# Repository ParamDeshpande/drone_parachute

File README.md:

# taxir 
This is the repository for the problem statement 
```
Develop a mechanism (can be software/ hardware/ both ) to deploy a parachute installed on the UAV in case of an emergency landing or power outage. The parachute is placed inside a compartment.
The expected output "Can be in the form of validated electronic circuit design, parachute deployment mechanism, CAD design, code, hardware"
(The code can be written in any programming language of your choice)
```
## Code
There are few versions of the code, please find the latest one in arduino_version. STM_32 mbed version is deprecated has memory overflow issues. 
find the cpp files in /main headers in /include.
 
## Setup

### Mainframe SETUP 

Please do install PlatformIO extension in VSCODE or the arduino IDE, in your pc/laptop depending on which architecture and which is being used or any other if you know what you are doing .... . and do install any HC-05 bluetooth serial terminal. Like [this one](https://play.google.com/store/apps/details?id=de.kai_morich.serial_bluetooth_terminal&hl=en). Or any other as per your preference.

### The system SETUP

Connect the backup battery and main battery in any order whatsover, the system should give an error and should fire the parachute initially cause one of the battery was missing. (new feature or setup init needs to be added here). That way even the end user is assured of the system working.
**HIT THE RESET BUTTON**
Connect your device to get debug via bluetooth, as to what is happening, if everything works out good, you will get debug message on bt stating all's good, else you might find the buzzer still irritating you. And there you go The system is up and ready.

## Conditions 
To eject the parachute, we apply the condition that it must reach a certain speed (1.5 m/s) or more within a specified time interval (0.25 s)
ie an acceleration of about 6m/secsq
. Otherwise, the parachute will not be ejected. Under such conditions, the drone is not allowed to reach a dangerous fall speed.

## Effects ( aka what all is done )
Once the parachute deploys, the system stops the spinning rotors to avoid entanglement with the parachute cords and reduces the risk of laceration injuries to people on the ground.
If battery dies out
relays releases spring support for the chute lid , 
Manual 
Release the flow for the chute aka stop powering the relay to hold the lid
Automatic 
FAILSAFE MECHANISM : The above mentioned in code. 

EITHER WAY OPENS under the given or desired conditions.

## PROTOTYPE GPB VERSION.

SEE  drone_parachute_pcb folder for board schematic.

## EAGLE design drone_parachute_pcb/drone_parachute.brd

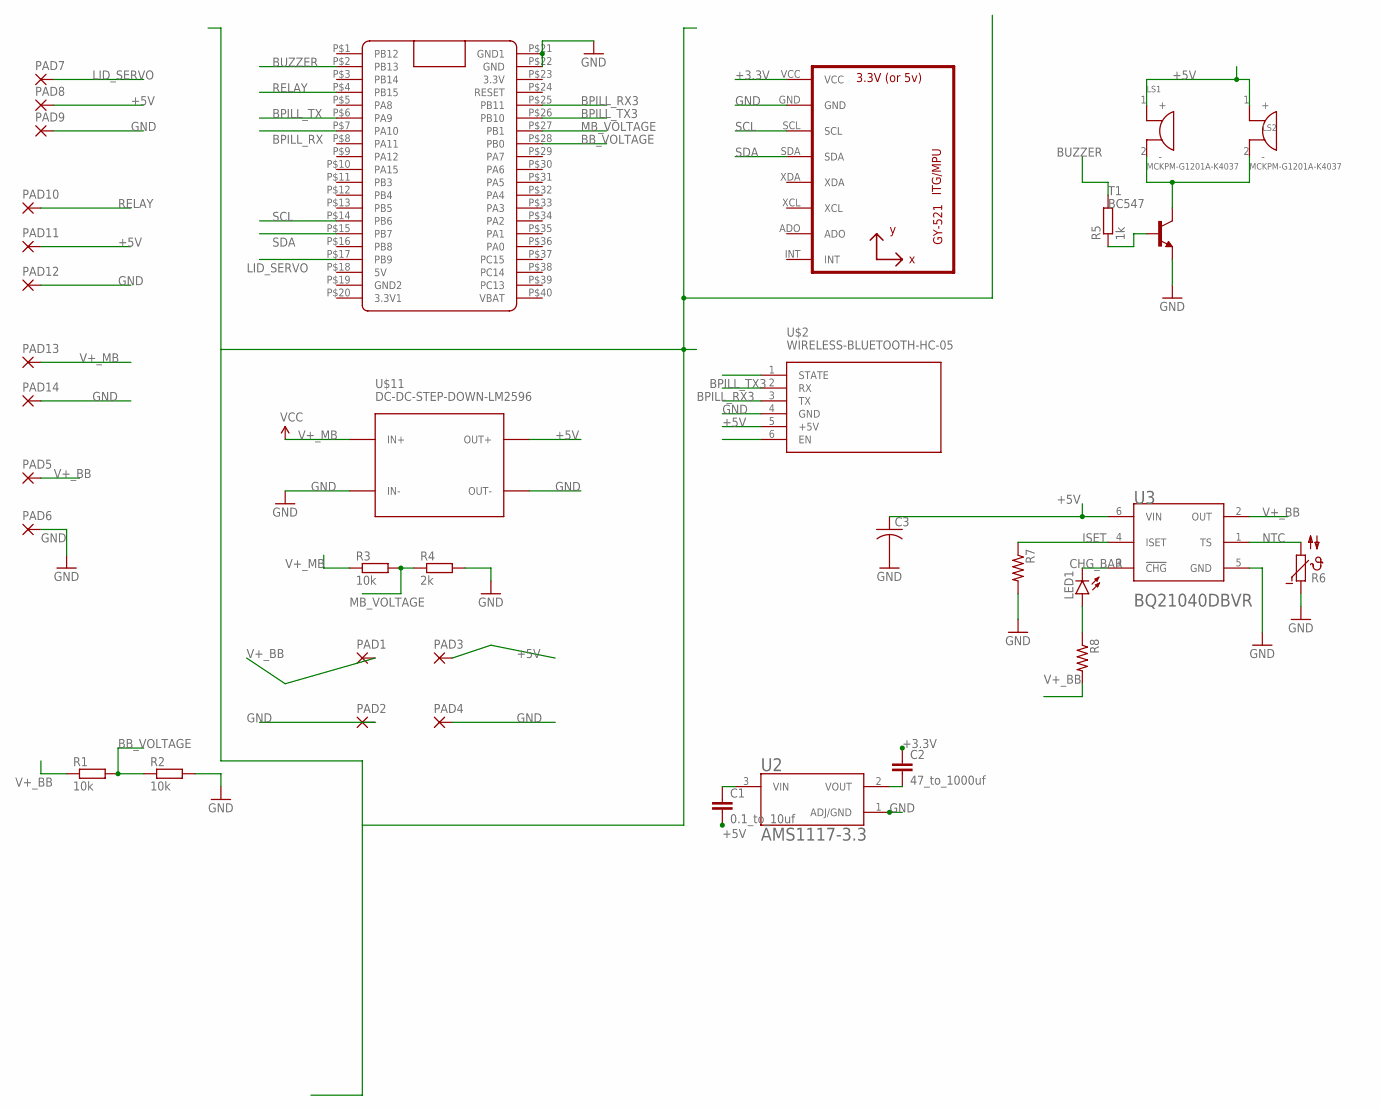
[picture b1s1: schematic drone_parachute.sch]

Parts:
C1: 0.1_to_10uf; C025-025X050
C2: 47_to_1000uf; C025-025X050
C3: C-USC0805; C0805
LED1: LEDCHIP-LED0805; CHIP-LED0805
LS1, LS2: MCKPM-G1201A-K4037; XDCR_MCKPM-G1201A-K4037
PAD1, PAD2, PAD3, PAD4, PAD5, PAD6, PAD7, PAD8, PAD9, PAD10, PAD11, PAD12, PAD13, PAD14: 1,6/0,8
R1, R2, R3: 10k; 0204/7
R4: 2k; 0204/7
R5: 1k; 0204/7
R6: NTC640; P640
R7, R8: R-US_R0805; R0805
T1: BC547; TO92
U1: GY-521MPU6050; GY-521
U2: AMS1117-3.3; SOT229P700X180-4N
U3: TEXAS_INSTRUMENTS_BQ21040DBVRTEXAS_INSTRUMENTS_BQ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; TEXAS_INSTRUMENTS_BQ21040DBVR_0
U$1: BLUE_PILL
U$2: WIRELESS-BLUETOOTH-HC-05
U$11: DC-DC-STEP-DOWN-LM2596

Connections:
+3.3V: C2.1, U1.VCC
+5V: C1.2, C3.1, LS1.1 (+), LS2.1 (+), PAD3.1, PAD8.1, PAD11.1, U3.6 (VIN), U$2.5 (+5V), U$11.OUT+
BB_VOLTAGE: R1.2, R2.1, U$1.P$28 (PB0)
BPILL_RX: U$1.P$7 (PA10)
BPILL_RX3: U$1.P$25 (PB11), U$2.3 (TX)
BPILL_TX: U$1.P$6 (PA9)
BPILL_TX3: U$1.P$26 (PB10), U$2.2 (RX)
BUZZER: R5.2, U$1.P$2 (PB13)
CHG_BAR: LED1.C, U3.3 (!CHG!)
GND: C3.2, PAD2.1, PAD4.1, PAD6.1, PAD9.1, PAD12.1, PAD14.1, R2.2, R4.2, R6.1, R7.2, T1.1 (E), U1.GND, U2.1 (ADJ/GND), U3.5 (GND), U$1.P$21 (GND1), U$1.P$22 (GND), U$2.4 (GND), U$11.IN-, U$11.OUT-
ISET: R7.1, U3.4 (ISET)
LID_SERVO: PAD7.1, U$1.P$17 (PB9)
MB_VOLTAGE: R3.2, R4.1, U$1.P$27 (PB1)
unnamed: C1.1, U2.3 (VIN)
unnamed: R5.1, T1.2 (B)
unnamed: C2.2, U2.2 (VOUT)
unnamed: LED1.A, R8.1
unnamed: LS1.2 (-), LS2.2 (-), T1.3 (C)
NTC: R6.2, U3.1 (TS)
RELAY: PAD10.1, U$1.P$4 (PB15)
SCL: U1.SCL, U$1.P$14 (PB6)
SDA: U1.SDA, U$1.P$15 (PB7)
V+_BB: PAD1.1, PAD5.1, R1.1, R8.2, U3.2 (OUT)
V+_MB: PAD13.1, R3.1, U$11.IN+

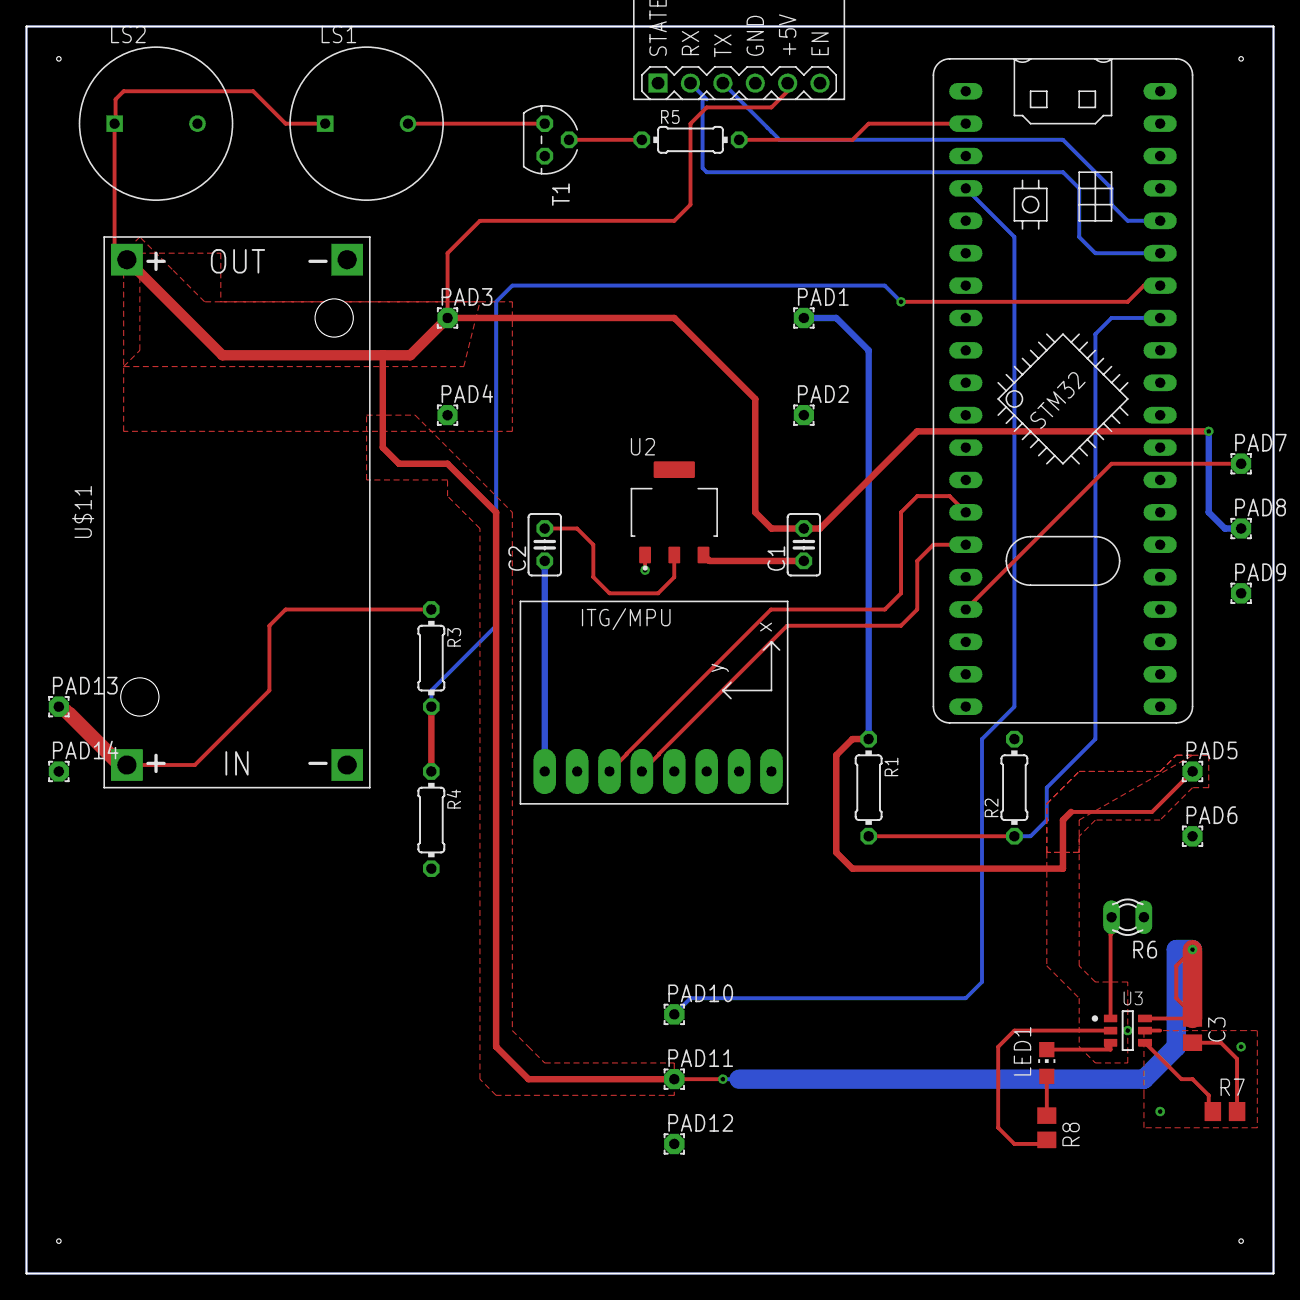
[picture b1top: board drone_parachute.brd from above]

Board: 2 copper layers, 97.8 x 97.8 mm, 35 parts (0 on the bottom side), 22 nets.

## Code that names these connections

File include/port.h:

#ifndef PORT_H
#define PORT_H

//enum PIN_Nos{PA2,PA3,PB0,PB1,PB6,PB7,PB9,PB13,PB15,PC13};


const int RX = (PA3) ;
const int TX = (PA2) ;
const int SCL = (PB6) ;
const int SDA = (PB7) ;
const int LED_PIN = (PC13);
const int SERVO_PIN = (PB9);
const int RELAY_PIN = (PB15);
const int BUZZER_PIN = (PB13);
const int MAIN_BAT_VOLT_PIN = (PB1);
const int BACKUP_BAT_VOLT_PIN = (PB0);

#endif // !PORT_H

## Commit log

2020-01-04 added things from taxir task2
2020-01-04 blink led code works
2020-01-05 added lot of things
2020-01-08 added code for arduino version
2020-01-08 arduino works only when files are named as .ino
2020-01-08 firsst commit
2020-01-08 big picture commit
2020-01-09 partially written battery.ino
2020-01-09 changed src to main and added include folder in main
2020-01-09 big picutre commit
2020-01-09 big picture commit #3
2020-01-09 big commit
2020-01-16 added PCB design.
2020-01-16 added GPB images.
2020-01-16 added img in readme
2020-01-17 remove submodule
2020-01-18 changed vscode THEME
2020-01-18 added and tested bluetooth code.
2020-01-18 added captains logs
2020-01-18 tested code for demostration.
2020-01-20 edited README.
2020-01-27 added instructions video.
2020-02-15 added Ti's charging IC details.
2020-02-23 added Ti's charging IC schematic.
2020-03-08 added board .brd for charging IC.
2020-03-08 reedited all gerber files for newer needs.

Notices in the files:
parts and their libraries:
diy-modules: Released under the Creative Commons Attribution 4.0 International License: http://creativecommons.org/licenses/by/4.0
SparkFun: Licensing: CC v3.0 Share-Alike You are welcome to use this library for commercial purposes.
